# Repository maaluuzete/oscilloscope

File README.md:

# Oscilloscope

A small portable oscilloscope, made with curiosity! I'm a **technical high school student in Electrotechnics**, and during one full semester we studied oscilloscopes: how they work, how signals are displayed, how to read time and voltage scales, trigger behavior, measurements, and practical use in electronics labs.  
At some point, a thought naturally came up: now that I understand how an oscilloscope works… why not build one myself
So I did hihi!
This project is a compact digital oscilloscope, including schematic, PCB, firmware, and even the case design.  
It features a color TFT display with a classic oscilloscope grid, adjustable vertical and horizontal scales, configurable trigger (rising or falling edge), and automatic measurements such as Vpp, Vrms, and signal frequency.  
The interface is controlled using rotary encoders, and the device boots with a custom splash screen, because instruments can be functional and cute. The overall aesthetic was intentionally designed to be soft and friendly, with pastel tones and a personal touch that makes it feel less like a lab instrument and more like something made by a person who genuinely enjoys electronics.

## Screenshots

## Project Structure
```
/
├── case/
│ ├── toposciloscopio.step
│ ├── toposciloscopio.stl
│ ├── osciloscopiocase.step
│ └── osciloscopiocase.stl
│
├── firmware/
│ ├── osciloscopio_firmware.ino
│ └── test.py
│
├── images/
│ ├── case.png
│ ├── oscilloscopio_3d.png
│ ├── oscilloscopio_pcb.png
│ ├── oscilloscopio_schematic.png
│ └── top.png
│
├── pcb/
│ ├── gerbers/
│ ├── osciloscopio.csv
│ ├── osciloscopio.kicad_pcb
│ ├── osciloscopio.kicad_pro
│ └── osciloscopio.kicad_sch
├── LICENSE
└── README.md
```

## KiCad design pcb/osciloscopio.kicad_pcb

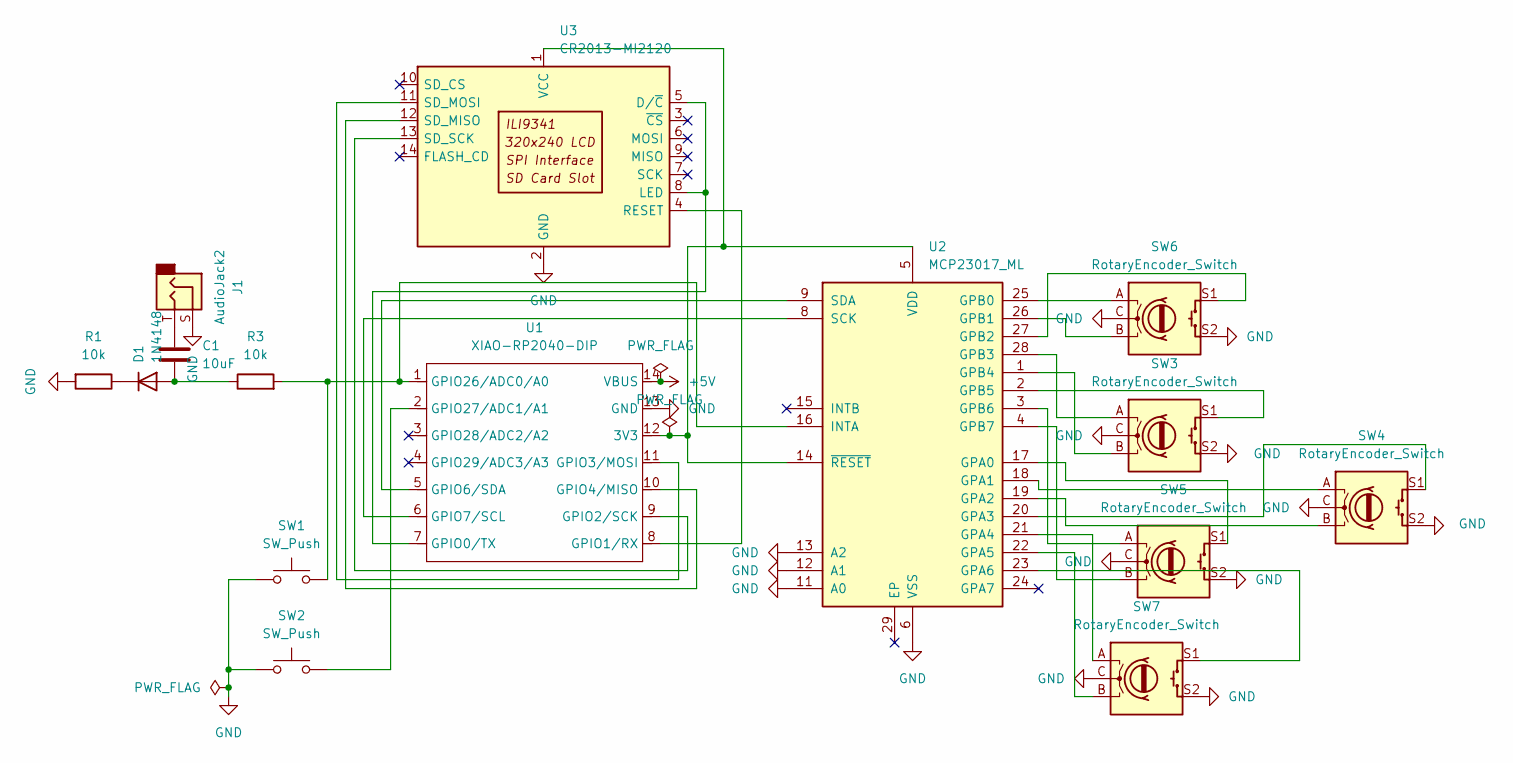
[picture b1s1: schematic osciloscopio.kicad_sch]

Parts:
C1: 10uF; C_0805_2012Metric
D1: 1N4148; D_DO-35_SOD27_P7.62mm_Horizontal
J1: AudioJack2; Jack_3.5mm_PJ320D_Horizontal
R1, R3: 10k; R_0805_2012Metric
SW1, SW2: SW_Push; SW_Cherry_MX_1.00u_PCB
SW3, SW4, SW5, SW6, SW7: RotaryEncoder_Switch; RotaryEncoder_Alps_EC11E-Switch_Vertical_H20mm
U1: XIAO-RP2040-DIP
U2: MCP23017_ML; QFN-28-1EP_6x6mm_P0.65mm_EP4.25x4.25mm
U3: CR2013-MI2120

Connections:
+5V: U1.14 (VBUS)
GND: J1.S, R1.2, SW1.1, SW2.1, SW3.C, SW3.S2, SW4.C, SW4.S2, SW5.C, SW5.S2, SW6.C, SW6.S2, SW7.C, SW7.S2, U1.13 (GND), U2.6 (VSS), U2.11 (A0), U2.12 (A1), U2.13 (A2), U3.2 (GND)
unnamed: C1.1, J1.T
unnamed: C1.2, D1.2 (A), R3.1
unnamed: D1.1 (K), R1.1
unnamed: U1.12 (3V3), U2.5 (VDD), U2.14 (~RESET), U3.1 (VCC)
unnamed: U1.7 (GPIO0/TX), U3.5 (D/~C), U3.8 (LED)
unnamed: U1.8 (GPIO1/RX), U3.4 (RESET)
unnamed: U1.9 (GPIO2/SCK), U3.13 (SD_SCK)
unnamed: U1.11 (GPIO3/MOSI), U3.11 (SD_MOSI)
unnamed: U1.10 (GPIO4/MISO), U3.12 (SD_MISO)
unnamed: U1.5 (GPIO6/SDA), U2.9 (SDA)
unnamed: U1.6 (GPIO7/SCL), U2.8 (SCK)
unnamed: R3.2, SW1.2, U1.1 (GPIO26/ADC0/A0), U2.16 (INTA)
unnamed: SW2.2, U1.2 (GPIO27/ADC1/A1)
unnamed: SW5.S1, U2.17 (GPA0)
unnamed: SW4.A, U2.18 (GPA1)
unnamed: SW4.B, U2.19 (GPA2)
unnamed: SW4.S1, U2.20 (GPA3)
unnamed: SW7.A, U2.21 (GPA4)
unnamed: SW7.B, U2.22 (GPA5)
unnamed: SW7.S1, U2.23 (GPA6)
unnamed: SW6.A, U2.25 (GPB0)
unnamed: SW6.B, U2.26 (GPB1)
unnamed: SW6.S1, U2.27 (GPB2)
unnamed: SW3.A, U2.28 (GPB3)
unnamed: SW3.B, U2.1 (GPB4)
unnamed: SW3.S1, U2.2 (GPB5)
unnamed: SW5.A, U2.3 (GPB6)
unnamed: SW5.B, U2.4 (GPB7)

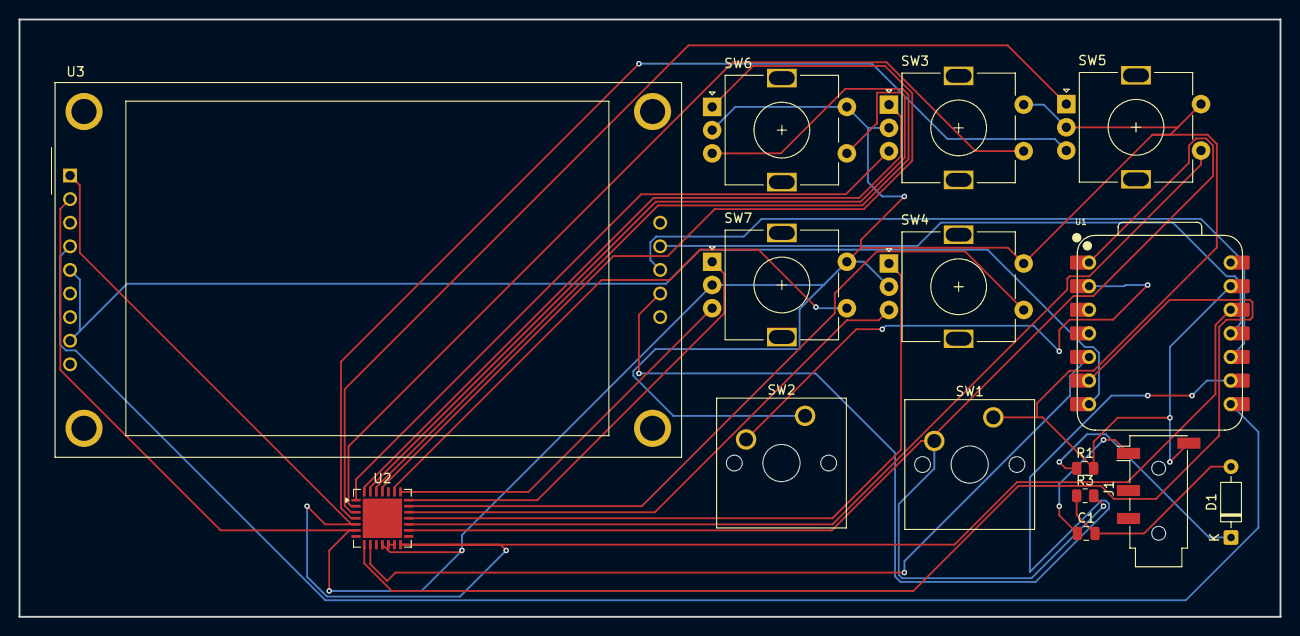
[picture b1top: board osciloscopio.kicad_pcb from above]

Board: 2 copper layers, 135.7 x 64.3 mm, 15 parts (0 on the bottom side), 29 nets.

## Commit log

2026-01-26 Refactor code structure for improved readability and maintainability
2026-01-26 Revise component details in osciloscopio.csv
    Updated component list in osciloscopio.csv.
2026-01-30 Its finished! The firmware and the readme.md
2026-01-30 Update README to use images instead of links
2026-01-30 bom.csv finished
